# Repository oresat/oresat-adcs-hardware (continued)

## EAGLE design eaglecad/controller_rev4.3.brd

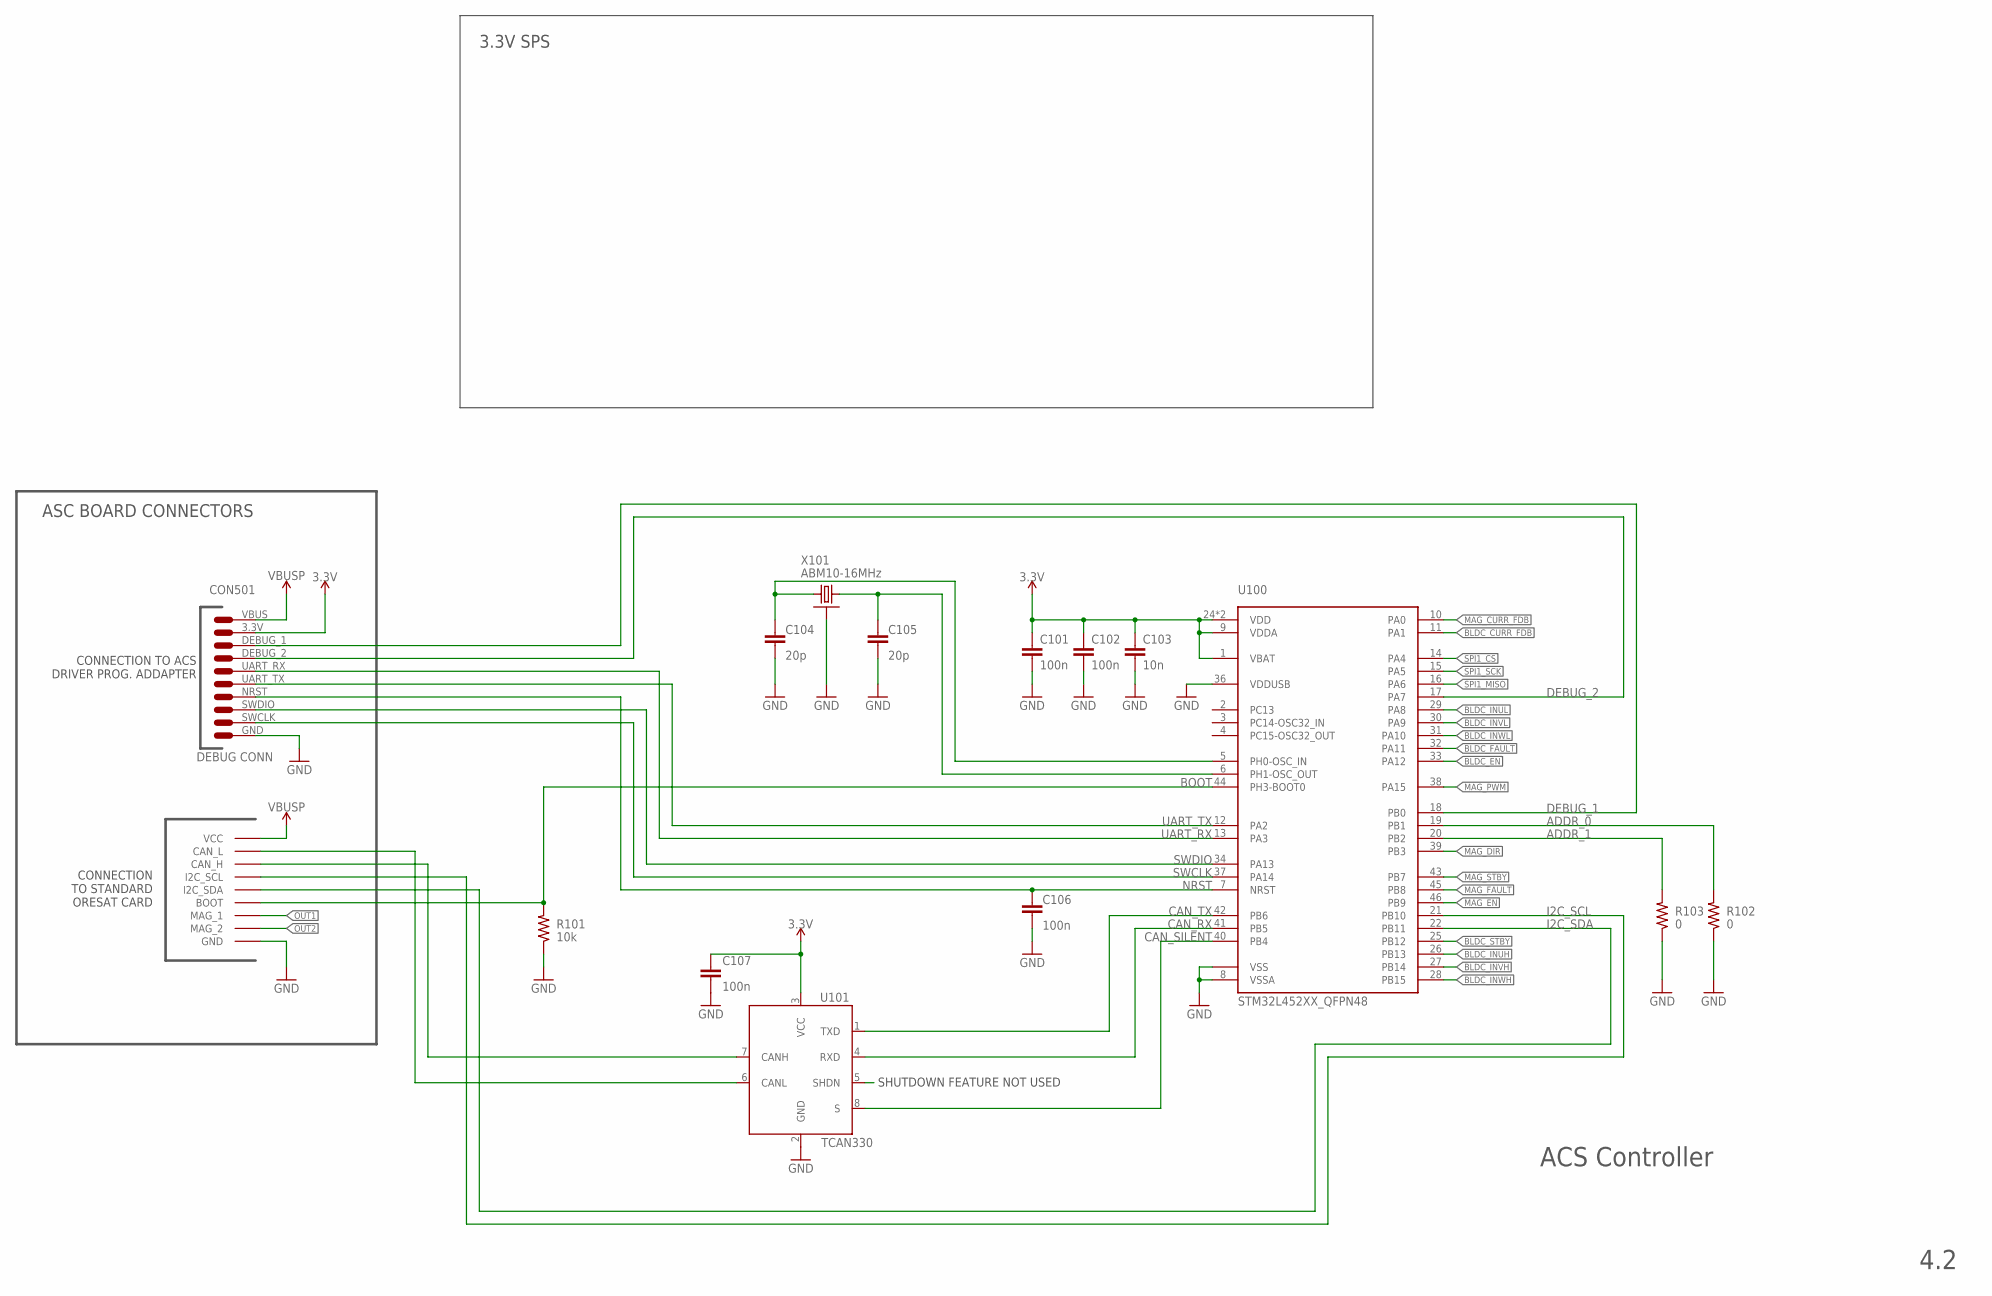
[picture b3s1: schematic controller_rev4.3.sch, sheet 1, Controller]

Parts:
C101, C102, C107: 100n; .0402-B-NOSILK; MPN CL05B104KO5NNNC
C103: 10n; .0402-B-NOSILK; MPN CL05B104KO5NNNC
C104, C105: 20p; .0402-B-NOSILK; MPN CL05C200JB51PNC
C106: 100n; .0402-B-NOSILK; MPN CL05C200JB51PNC
C501: DEBUG_CON
R101: 10k; .0402-B-NOSILK; MPN RC1005F6653CS
R102, R103: 0; .0402-B-NOSILK; MPN RC1005F6653CS
U100: STM32L452XX_QFPN48; QFPN-48
U101: TCAN330; SOT23-8_TI-DCN; MPN TCAN330GDCNT
U$2: MEZZANINE_1
X101: ABM10-16MHz; CRYSTAL_2.5X2; MPN ECS-160-10-36Q-ES-TR

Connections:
3.3V: C101.1, C102.1, C103.1, C107.1, C501.3.3V (2), U100.1 (VBAT), U100.9 (VDDA), U100.24 (VDD), U100.48 (VDD), U101.3 (VCC); also elsewhere on the board
ADDR_0: R102.2, U100.19 (PB1)
ADDR_1: R103.2, U100.20 (PB2)
BLDC_CURR_FDB: U100.11 (PA1); also elsewhere on the board
BLDC_EN: U100.33 (PA12); also elsewhere on the board
BLDC_FAULT: U100.32 (PA11); also elsewhere on the board
BLDC_INUH: U100.26 (PB13); also elsewhere on the board
BLDC_INUL: U100.29 (PA8); also elsewhere on the board
BLDC_INVH: U100.27 (PB14); also elsewhere on the board
BLDC_INVL: U100.30 (PA9); also elsewhere on the board
BLDC_INWH: U100.28 (PB15); also elsewhere on the board
BLDC_INWL: U100.31 (PA10); also elsewhere on the board
BLDC_STBY: U100.25 (PB12); also elsewhere on the board
BOOT: R101.2, U100.44 (PH3-BOOT0), U$2.P$9 (BOOT), U$2.P$22 (BOOT)
CAN_H: U101.7 (CANH), U$2.P$6 (CAN_H), U$2.P$25 (CAN_H)
CAN_L: U101.6 (CANL), U$2.P$5 (CAN_L), U$2.P$26 (CAN_L)
CAN_RX: U100.41 (PB5), U101.4 (RXD)
CAN_SHDN: U101.5 (SHDN)
CAN_SILENT: U100.40 (PB4), U101.8 (S)
CAN_TX: U100.42 (PB6), U101.1 (TXD)
CLK1: C104.1, U100.5 (PH0-OSC_IN), X101.3 (2)
CLK2: C105.1, U100.6 (PH1-OSC_OUT), X101.1
DEBUG_1: C501.DEBUG_1 (3), U100.18 (PB0)
DEBUG_2: C501.DEBUG_2 (4), U100.17 (PA7)
GND: C101.2, C102.2, C103.2, C104.2, C105.2, C106.2, C107.2, C501.GND (10), R101.1, R102.1, R103.1, U100.8 (VSSA), U100.23 (VSS), U100.35 (VSS), U100.36 (VDDUSB), U100.47 (VSS), U100.EPAD (VSS), U101.2 (GND), U$2.P$1 (GND), U$2.P$2 (GND), U$2.P$14 (GND), U$2.P$15 (GND), U$2.P$16 (GND), U$2.P$17 (GND), U$2.P$29 (GND), U$2.P$30 (GND), X101.2 (SHIELD), X101.4 (SHIELD); also elsewhere on the board
I2C_SCL: U100.21 (PB10), U$2.P$7 (I2C_SCL), U$2.P$24 (I2C_SCL)
I2C_SDA: U100.22 (PB11), U$2.P$8 (I2C_SDA), U$2.P$23 (I2C_SDA)
MAG_CURR_FDB: U100.10 (PA0); also elsewhere on the board
MAG_DIR: U100.39 (PB3); also elsewhere on the board
MAG_EN: U100.46 (PB9); also elsewhere on the board
MAG_FAULT: U100.45 (PB8); also elsewhere on the board
MAG_PWM: U100.38 (PA15); also elsewhere on the board
MAG_STBY: U100.43 (PB7); also elsewhere on the board
NRST: C106.1, C501.NRST (7), U100.7 (NRST)
OUT1: U$2.P$10 (MAG_1), U$2.P$21 (MAG_1); also elsewhere on the board
OUT2: U$2.P$11 (MAG_2), U$2.P$20 (MAG_2); also elsewhere on the board
SPI1_CS: U100.14 (PA4); also elsewhere on the board
SPI1_MISO: U100.16 (PA6); also elsewhere on the board
SPI1_SCK: U100.15 (PA5); also elsewhere on the board
SWCLK: C501.SWCLK (9), U100.37 (PA14)
SWDIO: C501.SWDIO (8), U100.34 (PA13)
UART_RX: C501.UART_RX (5), U100.13 (PA3)
UART_TX: C501.UART_TX (6), U100.12 (PA2)
VBUSP: C501.VBUS (1), U$2.P$3 (VCC), U$2.P$4 (VCC), U$2.P$12 (VCC), U$2.P$13 (VCC), U$2.P$18 (VCC), U$2.P$19 (VCC), U$2.P$27 (VCC), U$2.P$28 (VCC); also elsewhere on the board

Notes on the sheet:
ACS Controller
4.2
3.3V SPS
CONNECTION TO ACS DRIVER PROG. ADDAPTER
CONNECTION TO STANDARD ORESAT CARD
ASC BOARD CONNECTORS
CON501
DEBUG CONN
SHUTDOWN FEATURE NOT USED

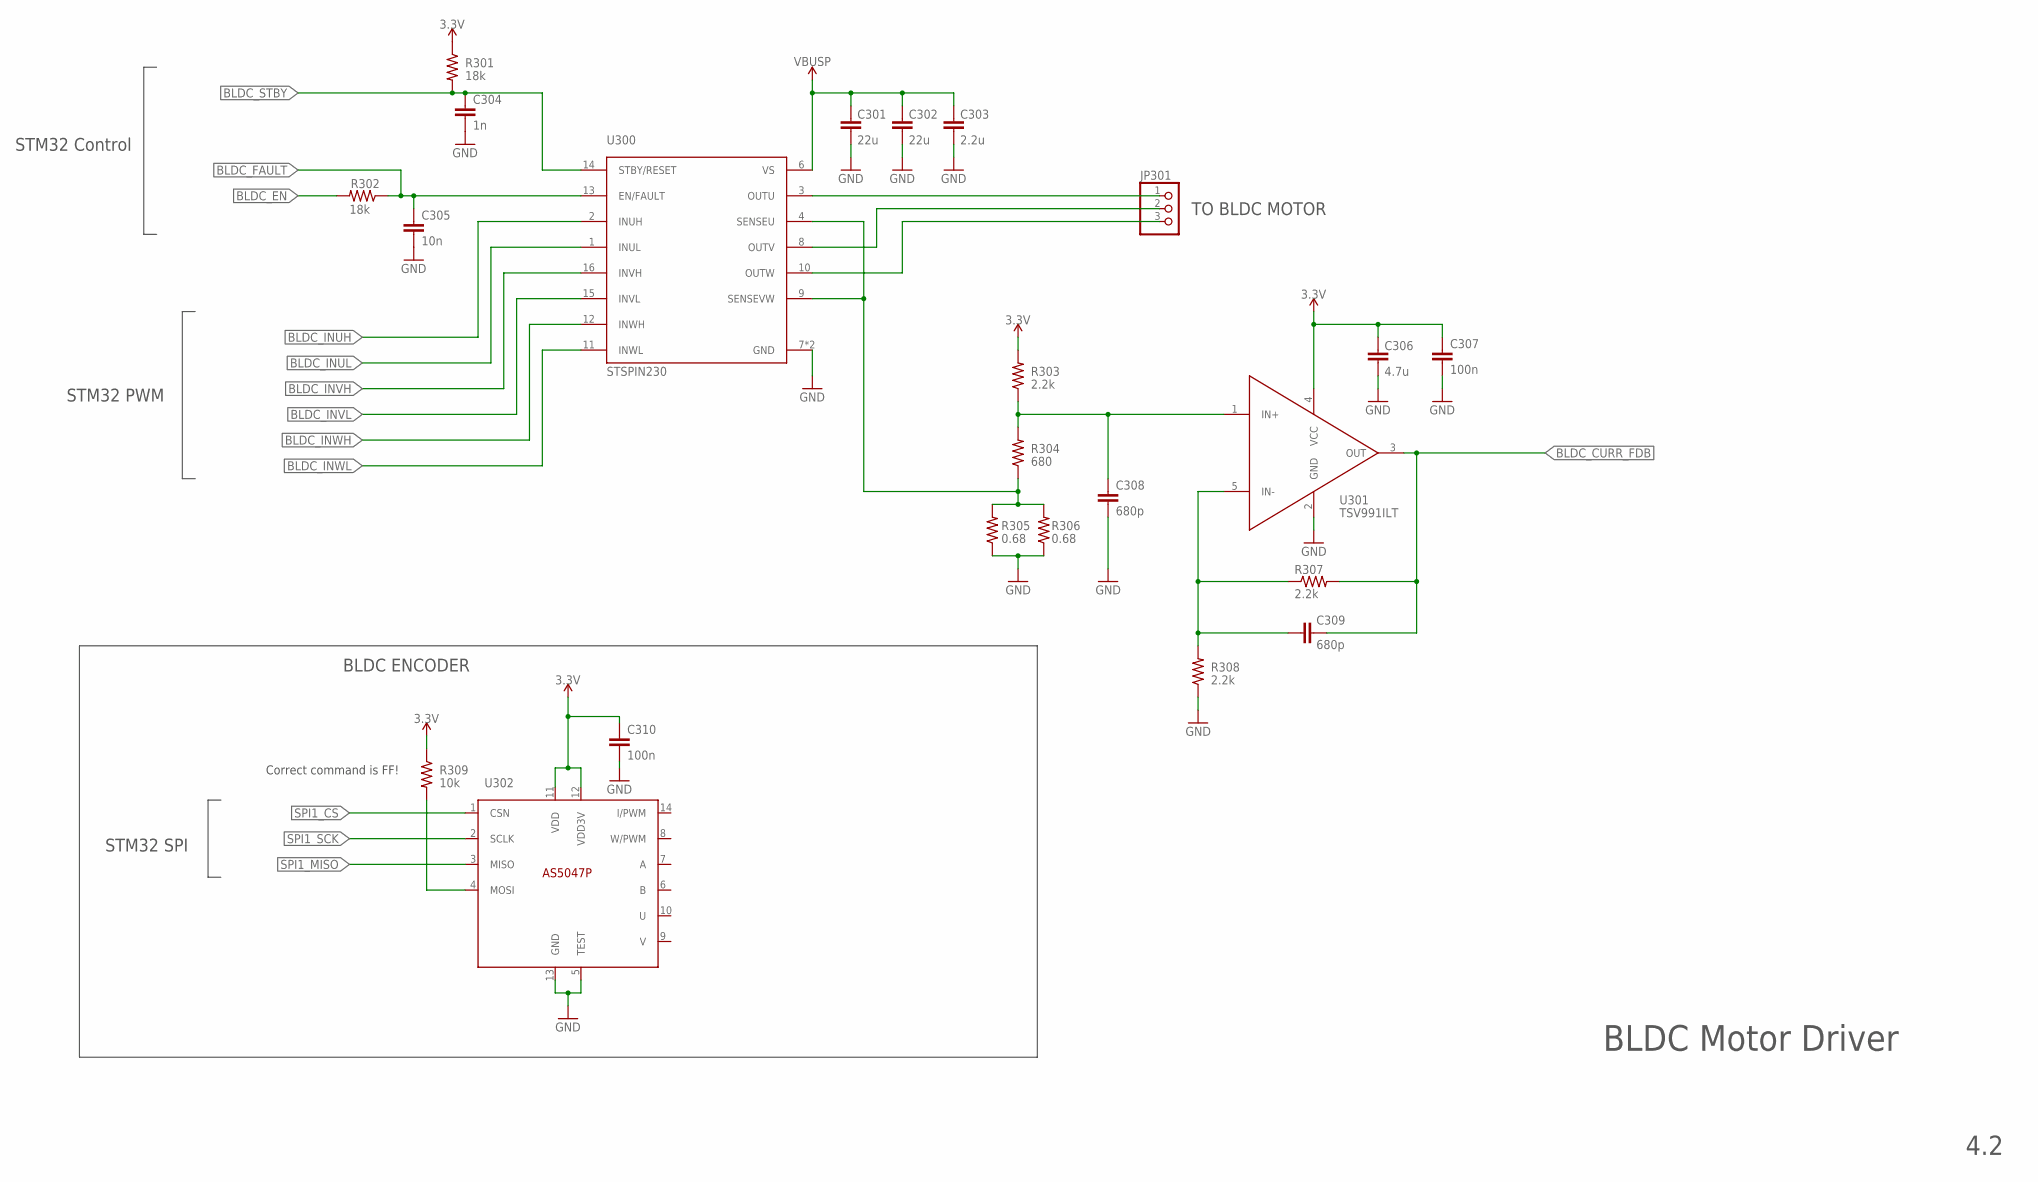
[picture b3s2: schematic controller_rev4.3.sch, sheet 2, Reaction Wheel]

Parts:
C301, C302: 22u; .0603-B-NOSILK; MPN CL05B104KO5NNNC
C303: 2.2u; .0603-B-NOSILK; MPN CL05B104KO5NNNC
C304: 1n; .0402-B-NOSILK; MPN CL05B104KO5NNNC
C305: 10n; .0402-B-NOSILK; MPN CL05B104KO5NNNC
C306: 4.7u; .0603-B-NOSILK; MPN CL05B104KO5NNNC
C307, C310: 100n; .0402-B-NOSILK; MPN CL05B104KO5NNNC
C308, C309: 680p; .0402-B-NOSILK; MPN CL05B104KO5NNNC
JP301: PINHD-1X03_2.00; 1X03M
R301, R302: 18k; .0402-B-NOSILK; MPN RC1005F6653CS
R303, R307, R308: 2.2k; .0402-B-NOSILK; MPN RC1005F6653CS
R304: 680; .0402-B-NOSILK; MPN RC1005F6653CS
R305, R306: 0.68; .0805-B-NOSILK
R309: 10k; .0402-B-NOSILK; MPN RC1005F6653CS
U300: STSPIN230; VFQPN
U301: TSV991ILT; SOT23-5
U302: AS5047P; TSSOP14

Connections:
3.3V: C306.1, C307.1, C310.1, R301.1, R303.2, R309.1, U301.4 (VCC), U302.11 (VDD), U302.12 (VDD3V); also elsewhere on the board
AS5047_MOSI: R309.2, U302.4 (MOSI)
BLDC_CURR_FDB: C309.1, R307.2, U301.3 (OUT); also elsewhere on the board
BLDC_EN: R302.2; also elsewhere on the board
BLDC_FAULT: C305.1, R302.1, U300.13 (EN/FAULT); also elsewhere on the board
BLDC_INUH: U300.2 (INUH); also elsewhere on the board
BLDC_INUL: U300.1 (INUL); also elsewhere on the board
BLDC_INVH: U300.16 (INVH); also elsewhere on the board
BLDC_INVL: U300.15 (INVL); also elsewhere on the board
BLDC_INWH: U300.12 (INWH); also elsewhere on the board
BLDC_INWL: U300.11 (INWL); also elsewhere on the board
BLDC_STBY: C304.1, R301.2, U300.14 (STBY/RESET); also elsewhere on the board
B_IN+: C308.1, R303.1, R304.2, U301.1 (IN+)
B_IN-: C309.2, R307.1, R308.2, U301.5 (IN-)
GND: C301.2, C302.2, C303.2, C304.2, C305.2, C306.2, C307.2, C308.2, C310.2, R305.1, R306.1, R308.1, U300.7 (GND), U300.EPAD (GND), U301.2 (GND), U302.5 (TEST), U302.13 (GND); also elsewhere on the board
SENSE_BLDC: R304.1, R305.2, R306.2, U300.4 (SENSEU), U300.9 (SENSEVW)
SPI1_CS: U302.1 (CSN); also elsewhere on the board
SPI1_MISO: U302.3 (MISO); also elsewhere on the board
SPI1_SCK: U302.2 (SCLK); also elsewhere on the board
U: JP301.1, U300.3 (OUTU)
V: JP301.2, U300.8 (OUTV)
VBUSP: C301.1, C302.1, C303.1, U300.6 (VS); also elsewhere on the board
W: JP301.3, U300.10 (OUTW)

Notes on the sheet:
TO BLDC MOTOR
BLDC Motor Driver
STM32 PWM
STM32 Control
Correct command is FF!
STM32 SPI
BLDC ENCODER
4.2

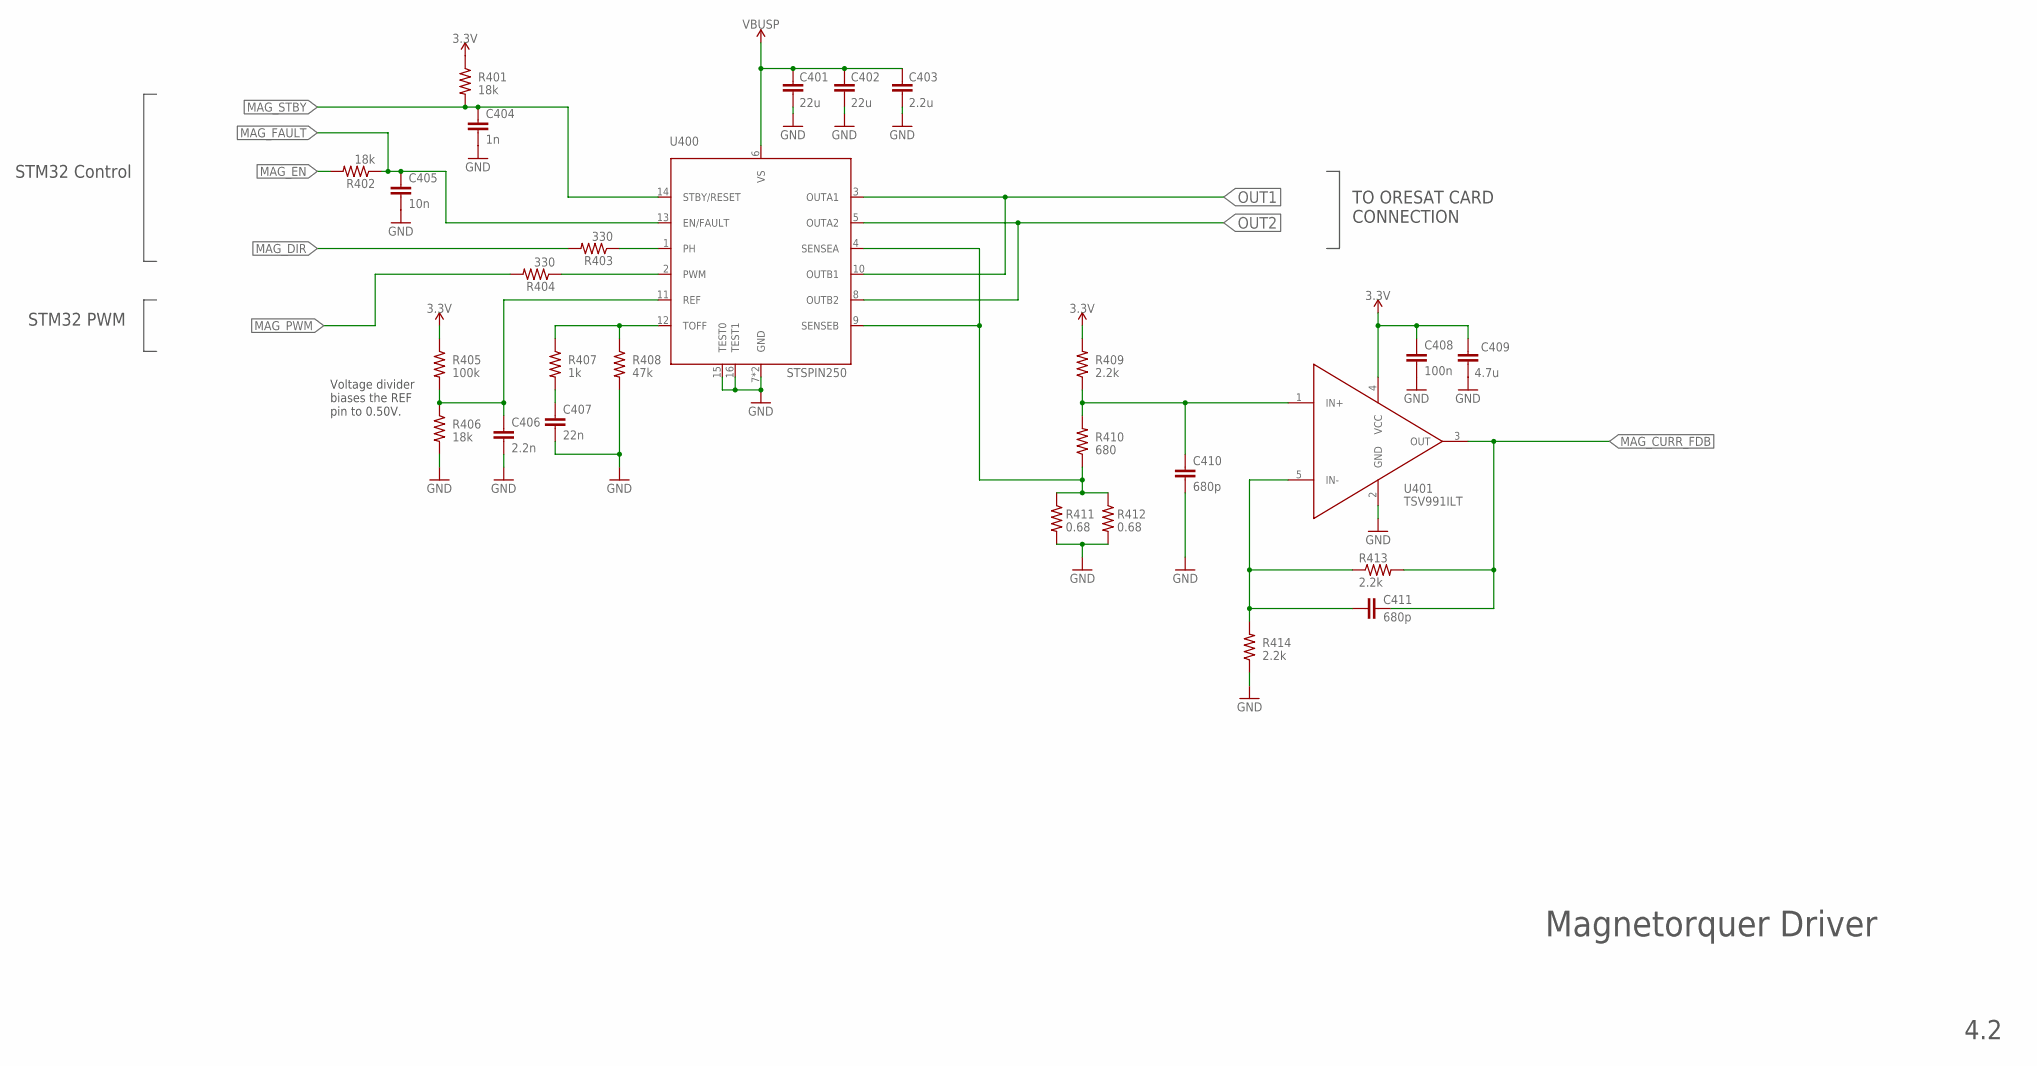
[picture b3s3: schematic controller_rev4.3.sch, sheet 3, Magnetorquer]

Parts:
C401, C402: 22u; .0603-B-NOSILK; MPN CL05B104KO5NNNC
C403: 2.2u; .0603-B-NOSILK; MPN CL05B104KO5NNNC
C404: 1n; .0402-B-NOSILK; MPN CL05B104KO5NNNC
C405: 10n; .0402-B-NOSILK; MPN CL05B104KO5NNNC
C406: 2.2n; .0402-B-NOSILK; MPN CL05B104KO5NNNC
C407: 22n; .0402-B-NOSILK; MPN CL05B104KO5NNNC
C408: 100n; .0402-B-NOSILK; MPN CL05B104KO5NNNC
C409: 4.7u; .0603-B-NOSILK; MPN CL05B104KO5NNNC
C410, C411: 680p; .0402-B-NOSILK; MPN CL05B104KO5NNNC
R401, R402, R406: 18k; .0402-B-NOSILK; MPN RC1005F6653CS
R403, R404: 330; .0402-B-NOSILK; MPN RC1005F6653CS
R405: 100k; .0402-B-NOSILK; MPN RC1005F6653CS
R407: 1k; .0402-B-NOSILK; MPN RC1005F6653CS
R408: 47k; .0402-B-NOSILK; MPN RC1005F6653CS
R409, R413, R414: 2.2k; .0402-B-NOSILK; MPN RC1005F6653CS
R410: 680; .0402-B-NOSILK; MPN RC1005F6653CS
R411, R412: 0.68; .0805-B-NOSILK
U400: STSPIN250; VFQPN
U401: TSV991ILT; SOT23-5

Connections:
3.3V: C408.1, C409.1, R401.1, R405.1, R409.2, U401.4 (VCC); also elsewhere on the board
250_REF: C406.1, R405.2, R406.1, U400.11 (REF)
250_TOFF: R407.1, R408.1, U400.12 (TOFF)
GND: C401.2, C402.2, C403.2, C404.2, C405.2, C406.2, C407.2, C408.2, C409.2, C410.2, R406.2, R408.2, R411.2, R412.2, R414.1, U400.7 (GND), U400.15 (TEST0), U400.16 (TEST1), U400.EPAD (GND), U401.2 (GND); also elsewhere on the board
MAG_CURR_FDB: C411.1, R413.2, U401.3 (OUT); also elsewhere on the board
MAG_DIR: R403.2; also elsewhere on the board
MAG_EN: R402.2; also elsewhere on the board
MAG_FAULT: C405.1, R402.1, U400.13 (EN/FAULT); also elsewhere on the board
MAG_PWM: R404.2; also elsewhere on the board
MAG_STBY: C404.1, R401.2, U400.14 (STBY/RESET); also elsewhere on the board
M_IN+: C410.1, R409.1, R410.2, U401.1 (IN+)
M_IN-: C411.2, R413.1, R414.2, U401.5 (IN-)
M_PH: R403.1, U400.1 (PH)
M_PWM: R404.1, U400.2 (PWM)
OUT1: U400.3 (OUTA1), U400.10 (OUTB1); also elsewhere on the board
OUT2: U400.5 (OUTA2), U400.8 (OUTB2); also elsewhere on the board
SENSE_MAG: R410.1, R411.1, R412.1, U400.4 (SENSEA), U400.9 (SENSEB)
TOFF1: C407.1, R407.2
VBUSP: C401.1, C402.1, C403.1, U400.6 (VS); also elsewhere on the board

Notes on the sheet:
TO ORESAT CARD CONNECTION
Magnetorquer Driver
Voltage divider biases the REF pin to 0.50V.
STM32 PWM
STM32 Control
4.2

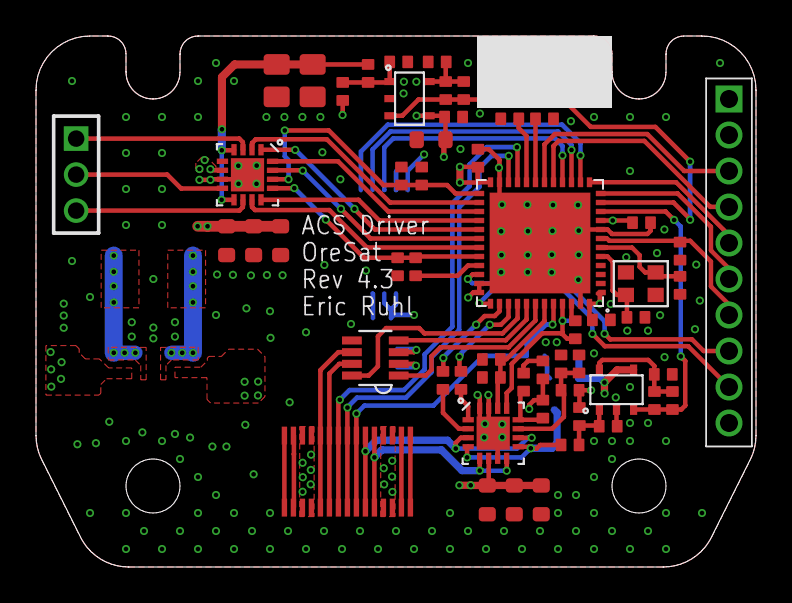
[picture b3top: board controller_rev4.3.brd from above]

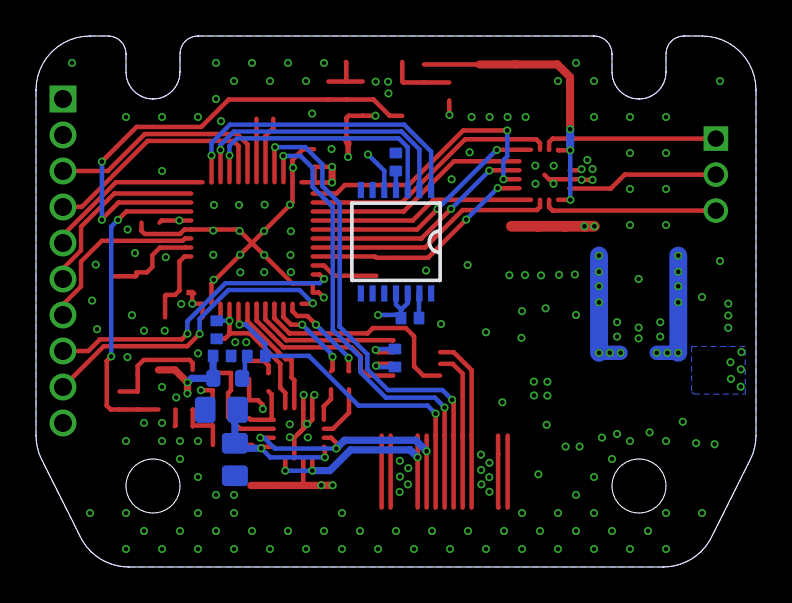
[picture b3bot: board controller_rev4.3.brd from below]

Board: 4 copper layers, 40.0 x 29.5 mm, 65 parts (10 on the bottom side), 58 nets.

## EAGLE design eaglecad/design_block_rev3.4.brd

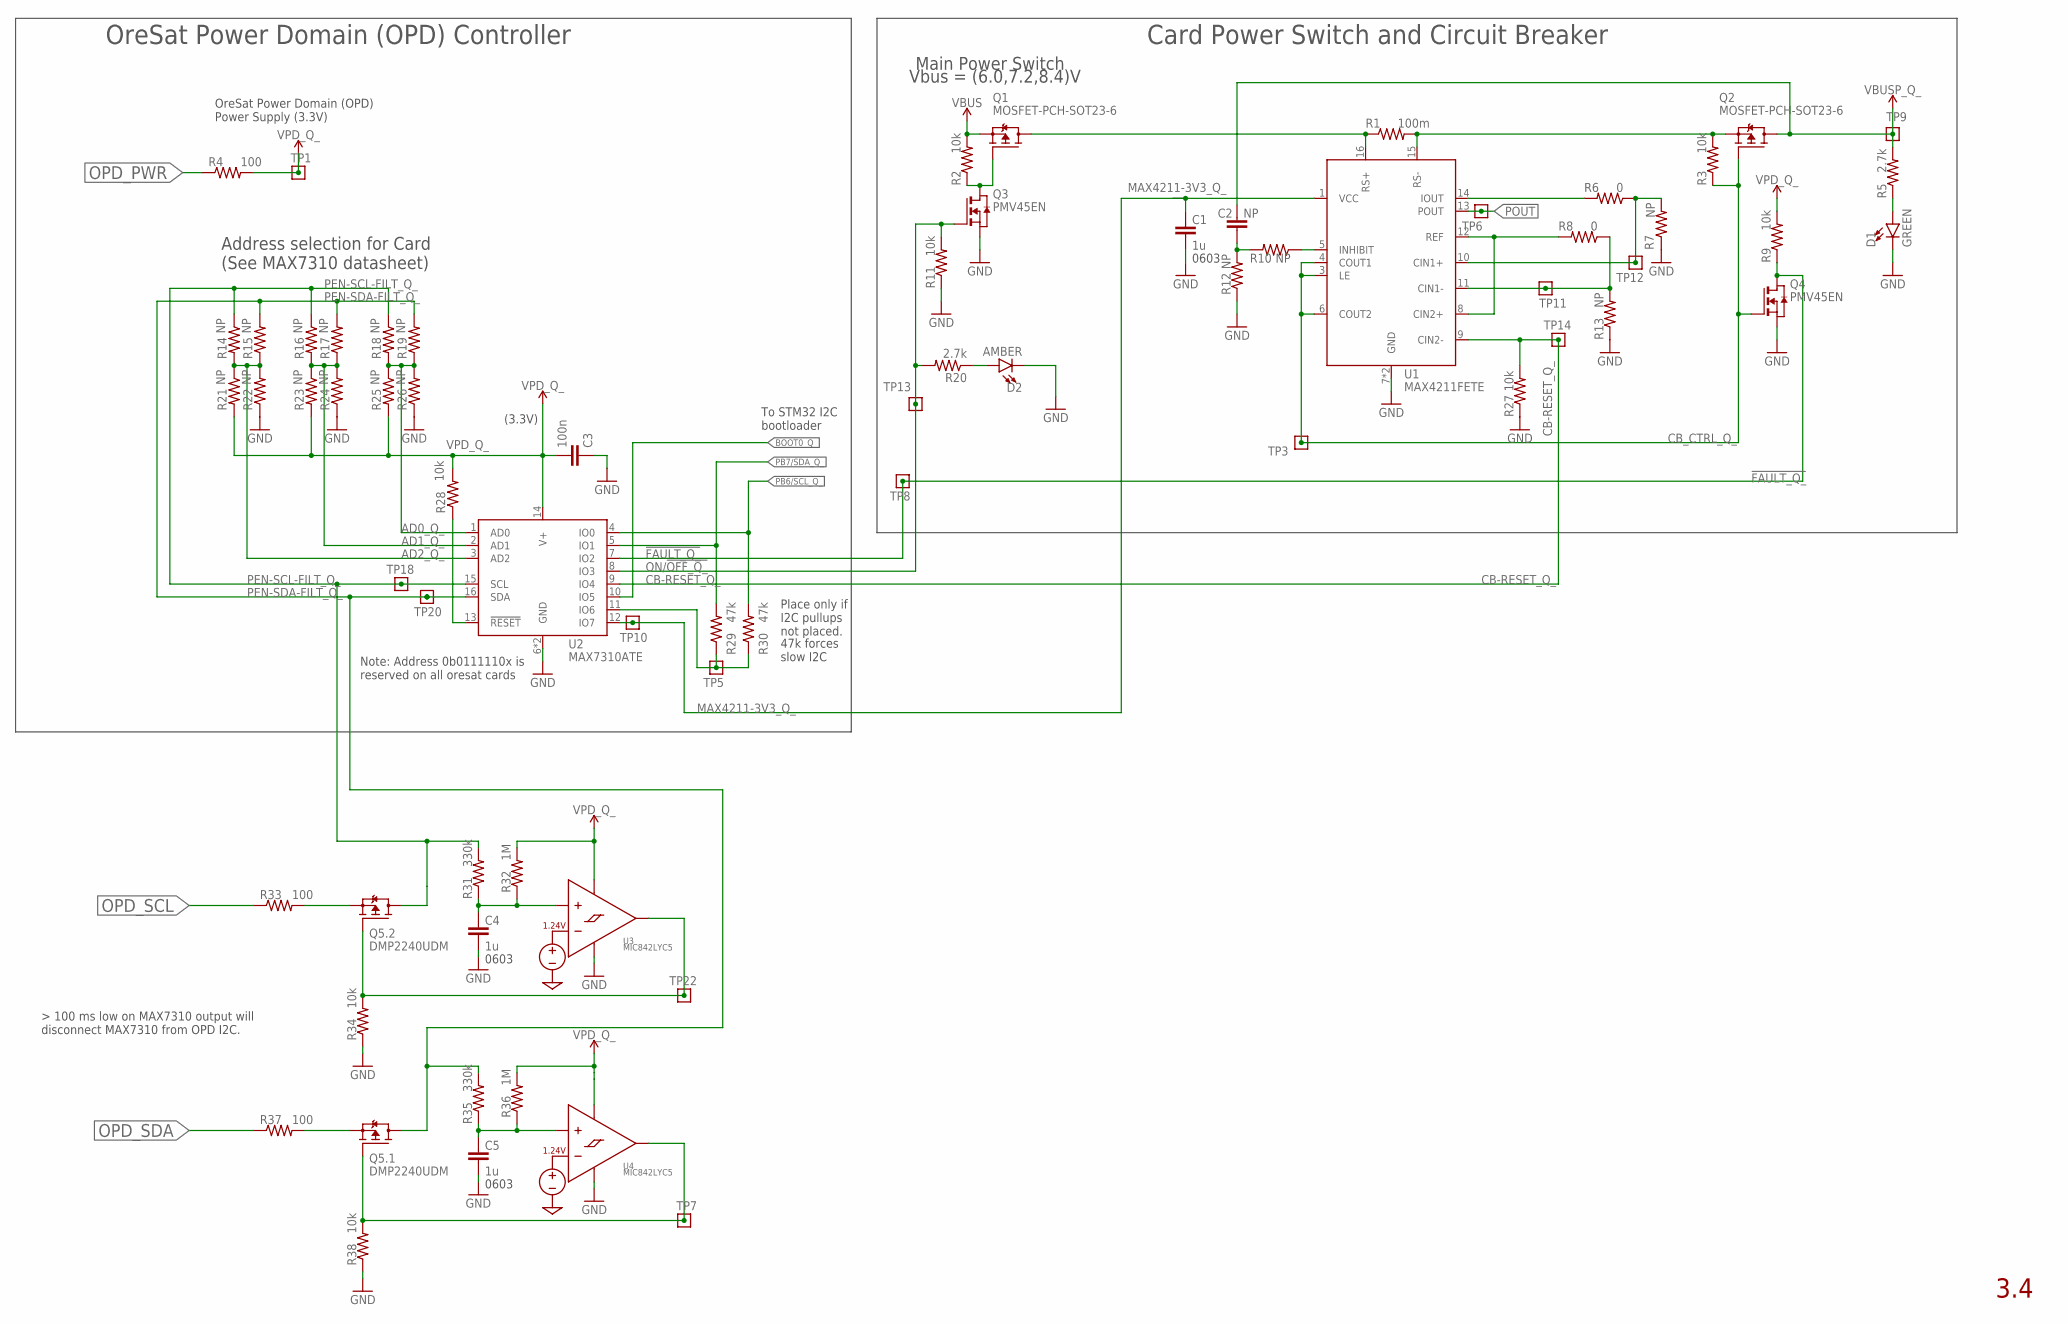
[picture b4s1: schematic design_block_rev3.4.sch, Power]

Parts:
C1, C4, C5: 1u; .0603-B-NOSILK; MPN CC0603KRX7R7BB105
C2: NP; .0402-B-NOSILK
C3: 100n; .0402-B-NOSILK; MPN CL05B104KO5NNNC
D1: GREEN; LED-0603; MPN SML-E12M8WT86
D2: AMBER; LED-0603; MPN IN-S63AT5A
Q1, Q2: MOSFET-PCH-SOT23-6; SOT23-6; MPN DMP3050LVT-7
Q3, Q4: PMV45EN; SOT23; MPN PMV45EN2R
Q5: DMP2240UDM; SOT23-6; MPN DMP2240UDM
R1: 100m; R1206; MPN CSR1206FTR100
R2, R3, R9, R11, R27, R28, R34, R38: 10k; .0402-B-NOSILK; MPN RC0402FR-0710KL
R4, R33, R37: 100; .0402-B-NOSILK; MPN RC0402FR-07100RL
R5, R20: 2.7k; .0402-B-NOSILK; MPN CRGCQ0402F2K7
R6, R8: 0; .0402-B-NOSILK; MPN RC0402JR-070RL
R7, R10, R12, R13, R14, R15, R16, R17, R18, R19, R21, R22, R23, R24, R25, R26: NP; .0402-B-NOSILK; MPN RC1005F6653CS
R29, R30: 47k; .0402-B-NOSILK; MPN RC0402FR-0747KL
R31, R35: 330k; .0402-B-NOSILK; MPN MCS04020C3303FE000
R32, R36: 1M; .0402-B-NOSILK; MPN RC0402FR-071ML
TP1, TP3, TP5, TP6, TP7, TP8, TP9, TP10, TP11, TP12, TP13, TP14, TP18, TP20, TP22: TEST-POINT; 2MM-TEST-POINT
U1: MAX4211FETE; QFN65P400X400X80-17T210; MPN MAX4211FETE
U2: MAX7310ATE; QFN65P400X400X80-17T210; MPN MAX7310ATE
U3, U4: MIC842LYC5; SC70-5

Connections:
!FAULT_Q_: Q4.3 (D), R9.1, TP8.1, U2.7 (IO2)
AD0_Q_: R18.2, R19.1, R25.1, R26.2, U2.1 (AD0)
AD1_Q_: R16.2, R17.1, R23.1, R24.2, U2.2 (AD1)
AD2_Q_: R14.2, R15.1, R21.1, R22.2, U2.3 (AD2)
BOOT0_Q_: U2.10 (IO5)
CB-RESET_Q_: R27.2, TP14.1, U1.9 (CIN2-), U2.9 (IO4)
CB_CTRL_Q_: Q2.3 (G), Q4.1 (G), R3.1, TP3.1, U1.3 (LE), U1.4 (COUT1), U1.6 (COUT2)
GND: C1.2, C3.1, C4.2, C5.2, D1.C, D2.C, Q3.2 (S), Q4.2 (S), R7.1, R11.1, R12.1, R13.1, R22.1, R24.1, R26.1, R27.1, R34.1, R38.1, U1.7 (GND), U1.EPAD (GND), U2.6 (GND), U2.EPAD (GND), U3.2 (GND), U4.2 (GND)
IOUT_Q_: R6.2, U1.14 (IOUT)
MAX4211-3V3_Q_: C1.1, TP10.1, U1.1 (VCC), U2.12 (IO7)
unnamed: D1.A, R5.1
unnamed: R29.1, R30.1, TP5.1, U2.11 (IO6)
unnamed: Q2.4 (S), R1.2, R3.2, U1.15 (RS-)
unnamed: C4.1, R31.1, R32.1, U3.1 (INP)
unnamed: C5.1, R35.1, R36.1, U4.1 (INP)
unnamed: Q5.2 (S), R33.2
unnamed: Q5.3 (G), R34.2, TP22.1, U3.4 (OUT)
unnamed: D2.A, R20.1
unnamed: Q5.5 (S), R37.2
unnamed: Q5.1 (G), R38.2, TP7.1, U4.4 (OUT)
unnamed: R28.1, U2.13 (!RESET)
unnamed: Q1.3 (G), Q3.3 (D), R2.1
unnamed: Q1.1 (D), Q1.2 (D), Q1.5 (D), Q1.6 (D), R1.1, U1.16 (RS+)
unnamed: R6.1, R7.2, TP12.1, U1.10 (CIN1+)
unnamed: R8.1, R13.2, TP11.1, U1.11 (CIN1-)
unnamed: R8.2, U1.8 (CIN2+), U1.12 (REF)
unnamed: C2.1, R10.2, R12.2
unnamed: R10.1, U1.5 (INHIBIT)
ON/!OFF_Q_: Q3.1 (G), R11.2, R20.2, TP13.1, U2.8 (IO3)
OPD_PWR: R4.1
OPD_SCL: R33.1
OPD_SDA: R37.1
PB6/SCL_Q_: R30.2, U2.4 (IO0)
PB7/SDA_Q_: R29.2, U2.5 (IO1)
PEN-SCL-FILT_Q_: Q5.4 (D), R14.1, R16.1, R18.1, R31.2, TP18.1, U2.15 (SCL)
PEN-SDA-FILT_Q_: Q5.6 (D), R15.2, R17.2, R19.2, R35.2, TP20.1, U2.16 (SDA)
POUT_Q_: TP6.1, U1.13 (POUT)
VBUS: Q1.4 (S), R2.2
VBUSP_Q_: C2.2, Q2.1 (D), Q2.2 (D), Q2.5 (D), Q2.6 (D), R5.2, TP9.1
VPD_Q_: C3.2, R4.2, R9.2, R21.2, R23.2, R25.2, R28.2, R32.2, R36.2, TP1.1, U2.14 (V+), U3.5 (VDD), U4.5 (VDD)

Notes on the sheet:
Main Power Switch
Address selection for Card (See MAX7310 datasheet)
(3.3V)
Vbus = (6.0,7.2,8.4)V
0603
OreSat Power Domain (OPD) Power Supply (3.3V)
OreSat Power Domain (OPD) Controller
Card Power Switch and Circuit Breaker
3.4
Note: Address 0b0111110x is reserved on all oresat cards
Place only if I2C pullups not placed.
47k forces slow I2C
To STM32 I2C bootloader

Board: 2 copper layers, 69 parts (64 on the bottom side), 36 nets, no tracks yet.

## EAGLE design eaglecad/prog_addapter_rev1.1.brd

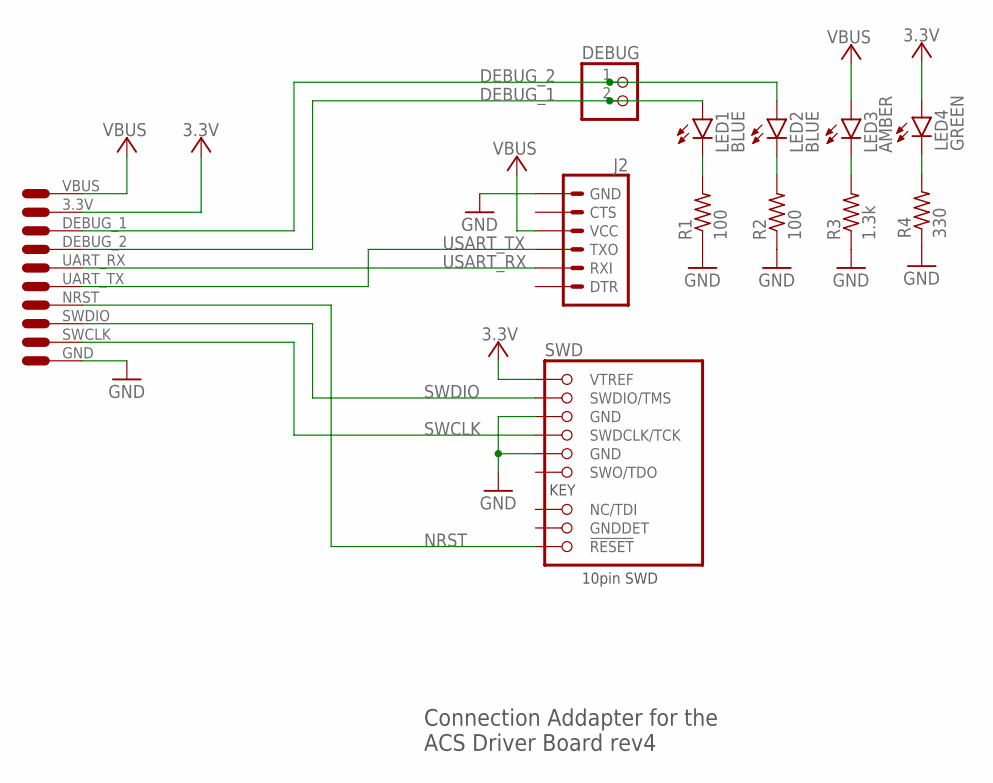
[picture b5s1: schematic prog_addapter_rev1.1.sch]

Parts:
DEBUG: PINHD-1X2; 1X02
J2: 6_PIN_SERIAL_TARGETSILK; 6_PIN_SERIAL_TARGET_SIDE_W_SILK
LED1, LED2: BLUE; CHIPLED_0603
LED3: AMBER; CHIPLED_0603
LED4: GREEN; CHIPLED_0603
R1, R2: 100; .0402-B-NOSILK
R3: 1.3k; .0402-B-NOSILK
R4: 330; .0402-B-NOSILK
SWD: 1.27MM-SWD-CONNECTOR; 1.27MM_2X5
U$1: DEBUG_CON

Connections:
3.3V: LED4.A, SWD.VTREF, U$1.3.3V (2)
DEBUG_1: DEBUG.1, LED2.A, U$1.DEBUG_1 (3)
DEBUG_2: DEBUG.2, LED1.A, U$1.DEBUG_2 (4)
GND: J2.P$6 (GND), R1.1, R2.1, R3.1, R4.1, SWD.GND, SWD.GND@2 (GND), U$1.GND (10)
unnamed: LED1.C, R1.2
unnamed: LED2.C, R2.2
unnamed: LED3.C, R3.2
unnamed: LED4.C, R4.2
NRST: SWD.!RESET, U$1.NRST (7)
SWCLK: SWD.SWDCLK (SWDCLK/TCK), U$1.SWCLK (9)
SWDIO: SWD.SWDIO (SWDIO/TMS), U$1.SWDIO (8)
USART_RX: J2.P$3 (RXI), U$1.UART_RX (5)
USART_TX: J2.P$2 (TXO), U$1.UART_TX (6)
VBUS: J2.P$4 (VCC), LED3.A, U$1.VBUS (1)

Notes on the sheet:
Connection Addapter for the ACS Driver Board rev4

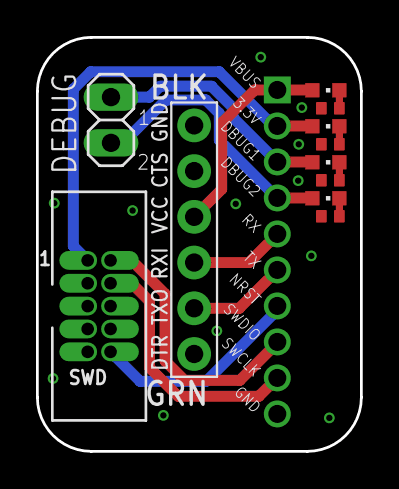
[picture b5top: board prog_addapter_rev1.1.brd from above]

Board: 2 copper layers, 18.0 x 23.0 mm, 12 parts (1 on the bottom side), 14 nets.
